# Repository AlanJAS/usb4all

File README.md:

# USB4all

USB4all es una placa para conectar sensores, actuadores y otros dispositivos electrónicos a una computadora mediante USB. Utiliza un **PIC18F4550** y organiza sus funcionalidades en módulos de firmware, con aplicaciones en el **Proyecto Butiá**.

El proyecto Butiá usa la placa USB4all (llamada USB4butia) con motores para crear una plataforma robótica educativa de bajo costo.

[Wiki Proyecto Butiá](https://www.fing.edu.uy/inco/proyectos/butia/mediawiki/index.php?title=Wiki_Buti%C3%A1)

Este repositorio reúne el firmware, el bootloader, diseños de placas, documentación técnica y una herramienta para grabar la aplicación por USB.

## Contenido

| Directorio | Contenido |
| --- | --- |
| [firmware/u4a2](firmware/u4a2/) | Firmware principal y módulos de usuario. |
| [firmware/bootloader](firmware/bootloader/) | Bootloader para instalar y actualizar la aplicación. |
| [fsusb-0.1.11-2](fsusb-0.1.11-2/) | Utilidad de programación USB incluida en el repositorio. |
| [pcb](pcb/) | Diseños de placas, sensores, actuadores y accesorios. |
| [doc](doc/) | Manuales, documentación del proyecto y del microcontrolador. |
| [usb4all_kernel_module](usb4all_kernel_module/) | Código histórico de un módulo para el kernel de Linux. |

## Ramas y herramientas

- **`master`**: desarrollo original, con proyectos para MPLAB C18.
- **[`xc8`](https://github.com/AlanJAS/usb4all/tree/xc8)**: migración a MPLAB XC8, con Makefiles independientes para la aplicación y el bootloader.

**Los comandos de compilación de este README corresponden a la rama `xc8`.** Los módulos opcionales y ejemplos históricos no están necesariamente migrados.

```sh
git clone --branch xc8 https://github.com/AlanJAS/usb4all.git
cd usb4all
```

Si ya tenés el repositorio:

```sh
git fetch origin
git switch xc8
```

## Compilar con XC8

### Requisitos

- GNU Make.
- MPLAB XC8 para PIC; los Makefiles están configurados para **XC8 4.00**.
- Pack **Microchip PIC18Fxxxx_DFP 1.7.171**.
- Python 3.9 o posterior para las comprobaciones de la aplicación.

El compilador y el pack de dispositivos se obtienen por separado:

- [MPLAB XC8](https://www.microchip.com/en-us/tools-resources/develop/mplab-xc-compilers/xc8)
- [Microchip Device Packs](https://packs.download.microchip.com/)

Los Makefiles utilizan estas rutas predeterminadas en Linux:

```text
XC8=/opt/microchip/xc8/v4.00/bin/xc8-cc
DFP=/opt/microchip/mplabx/v6.35/packs/Microchip/PIC18Fxxxx_DFP/1.7.171/xc8
```

`DFP` debe apuntar al subdirectorio `xc8` del pack.

### Aplicación

Desde la raíz del repositorio:

```sh
make -C firmware/u4a2
```

También podés ejecutar `make` directamente dentro de `firmware/u4a2`. El objetivo predeterminado compila y ejecuta las comprobaciones de la imagen.

Archivo para grabar por USB:

```text
firmware/u4a2/build/xc8/usb4all2.hex
```

Para repetir las comprobaciones o limpiar los resultados:

```sh
make -C firmware/u4a2 check
make -C firmware/u4a2 clean
```

### Bootloader

```sh
make -C firmware/bootloader
```

Archivo para grabar con un programador de hardware:

```text
firmware/bootloader/build/xc8/bootloader.hex
```

Para limpiar:

```sh
make -C firmware/bootloader clean
```

### Usar otras rutas

Las variables se pueden sobrescribir en la línea de comandos de cualquiera de los dos Makefiles:

```sh
make -C firmware/u4a2 \
  XC8=/otra/ruta/bin/xc8-cc \
  DFP=/otra/ruta/PIC18Fxxxx_DFP/1.7.171/xc8
```

Si el compilador está en el `PATH`, usá `XC8=xc8-cc`.

### Proyectos MPLAB

Se conservan proyectos de distintas etapas del desarrollo. Para reproducir la compilación descrita aquí, usá los Makefiles de `firmware/u4a2` y `firmware/bootloader`. Los proyectos y scripts de enlace de C18 no deben reutilizarse directamente para enlazar con XC8.

## Grabar la placa

### 1. Instalar el bootloader

Si el PIC no tiene el bootloader, necesitás un programador de hardware compatible, como PICkit.

1. Compilá el bootloader.
2. Conectá el programador según el pinout de tu placa.
3. Seleccioná el PIC18F4550 en el software del programador.
4. Grabá y verificá `firmware/bootloader/build/xc8/bootloader.hex`.

Luego podés cargar la aplicación por USB. **El HEX de la aplicación no incluye el bootloader**: en XC8 comienza en `0x08C0` y se genera sin bits de configuración.

### 2. Compilar fsusb

La utilidad incluida utiliza la API de **libusb 0.1** (`usb.h`, enlace con `-lusb`). Necesitás un compilador C, Make y las cabeceras y biblioteca compatibles con esa API; libusb 1.0 por sí sola no sustituye esta dependencia.

```sh
make -C fsusb-0.1.11-2
```

### 3. Entrar en modo bootloader

Con la placa conectada por USB:

1. Mantené presionado el botón de programación.
2. Pulsá y soltá el botón de reset.
3. Soltá el botón de programación.

Comprobá la identificación con:

```sh
lsusb
```

| Estado | VID:PID |
| --- | --- |
| Aplicación USB4all | `04d8:000c` |
| Bootloader | `04d8:000b` |

### 4. Grabar y ejecutar la aplicación

Desde la raíz del repositorio:

```sh
./fsusb-0.1.11-2/fsusb --program firmware/u4a2/build/xc8/usb4all2.hex
```

La opción `--program` graba y verifica. También podés verificar por separado:

```sh
./fsusb-0.1.11-2/fsusb --verify firmware/u4a2/build/xc8/usb4all2.hex
```

Para salir del bootloader y ejecutar la aplicación:

```sh
./fsusb-0.1.11-2/fsusb --reset
```

Comprobá que la placa vuelva a aparecer como `04d8:000c`.

Si el sistema deniega el acceso USB, revisá los permisos del dispositivo o las reglas udev de tu distribución. Para una operación puntual, podés ejecutar el comando de grabación con `sudo`.

## Arquitectura y módulos

El firmware base gestiona la comunicación USB, los módulos y los recursos compartidos. Cada módulo expone operaciones de inicialización, liberación y configuración, además de procesar sus comandos específicos.

En la rama `xc8`, los módulos activos se enumeran explícitamente en [module_registry.h](https://github.com/AlanJAS/usb4all/blob/xc8/firmware/u4a2/user/module_registry.h). Incluyen administración, detección de módulos, puertos, AX12, botones, motores y módulos de sensores y actuadores Butiá.

Para incorporar un módulo a esta compilación:

1. Implementá su descriptor y callbacks tomando como referencia un módulo activo de `firmware/u4a2/user/`.
2. Agregá sus fuentes y dependencias a `SOURCES` en el Makefile de la aplicación.
3. Declaralo y agregalo al final de `U4A_MODULES`, preservando el orden existente.
4. Compilá, ejecutá las comprobaciones y probá sus comandos en la placa.

Los índices dependen del orden del registro: el software de la computadora debe enumerar los módulos por nombre y no conservar índices de una imagen anterior. Los módulos compilados con C18 no son compatibles binariamente con XC8; hay que recompilar la aplicación.

## Comprobaciones y estado de la migración

La aplicación incluye comprobaciones de tamaños y disposición de estructuras, y un script que revisa el HEX y los símbolos generados: direcciones de la aplicación, vectores y ubicación de buffers USB, entre otros aspectos.

Estas comprobaciones no sustituyen las pruebas con la placa. La documentación de migración señala validaciones pendientes del intercambio USB, margen de pila y latencia bajo carga. Una compilación exitosa no demuestra por sí sola el funcionamiento completo en hardware.

El [documento de migración XC8](https://github.com/AlanJAS/usb4all/blob/xc8/firmware/u4a2/README-XC8.md) contiene detalles técnicos e historial de cambios. Algunas secciones conservan referencias a etapas anteriores, como `Makefile.xc8` o la ausencia de una migración del bootloader; para compilar, seguí los comandos anteriores y los Makefiles de la rama.

## Problemas frecuentes

| Problema | Qué revisar |
| --- | --- |
| No se encuentra `xc8-cc` | Sobrescribir `XC8` con la ruta de instalación. |
| Error al localizar el dispositivo o el pack | Revisar `DFP` y que termine en el subdirectorio `xc8`. |
| Falta `usb.h` o falla el enlace con `-lusb` | Instalar los archivos de desarrollo compatibles con libusb 0.1. |
| fsusb no detecta la placa para grabar | Comprobar el modo bootloader (`04d8:000b`), el cable y los permisos USB. |
| La placa no entra en modo bootloader | Comprobar que tenga instalado el bootloader y repetir la secuencia de botones. |
| La aplicación no arranca | Verificar la grabación, el bootloader, los bits de configuración y la compatibilidad del hardware. |

## Documentación y origen

- [USB4all: arquitectura y guía de uso](https://www.fing.edu.uy/inco/proyectos/butia/mediawiki/index.php?title=Usb4all)
- [Grabación del firmware](https://www.fing.edu.uy/inco/proyectos/butia/mediawiki/index.php?title=Usb4all#4._Grabando_el_Firmware)
- [Documentación incluida en el repositorio](doc/usb4all/)
- [Repositorio original en SourceForge](https://sourceforge.net/projects/usb4all/)

USB4all se originó como un trabajo de grado en Ingeniería en Computación de Aguirre, Fernández y Grossy. Su documentación y su integración con Butiá se publican en el sitio de la Facultad de Ingeniería de la Universidad de la República, Uruguay.

## Licencias

La documentación original presenta USB4all bajo **GNU GPL v2**. El repositorio también contiene componentes de terceros con avisos propios, incluidos fuentes de Microchip. Consultá las cabeceras y los archivos de licencia de cada componente antes de reutilizarlo o redistribuirlo.

La licencia de la utilidad fsusb está incluida en [fsusb-0.1.11-2/COPYING](fsusb-0.1.11-2/COPYING).

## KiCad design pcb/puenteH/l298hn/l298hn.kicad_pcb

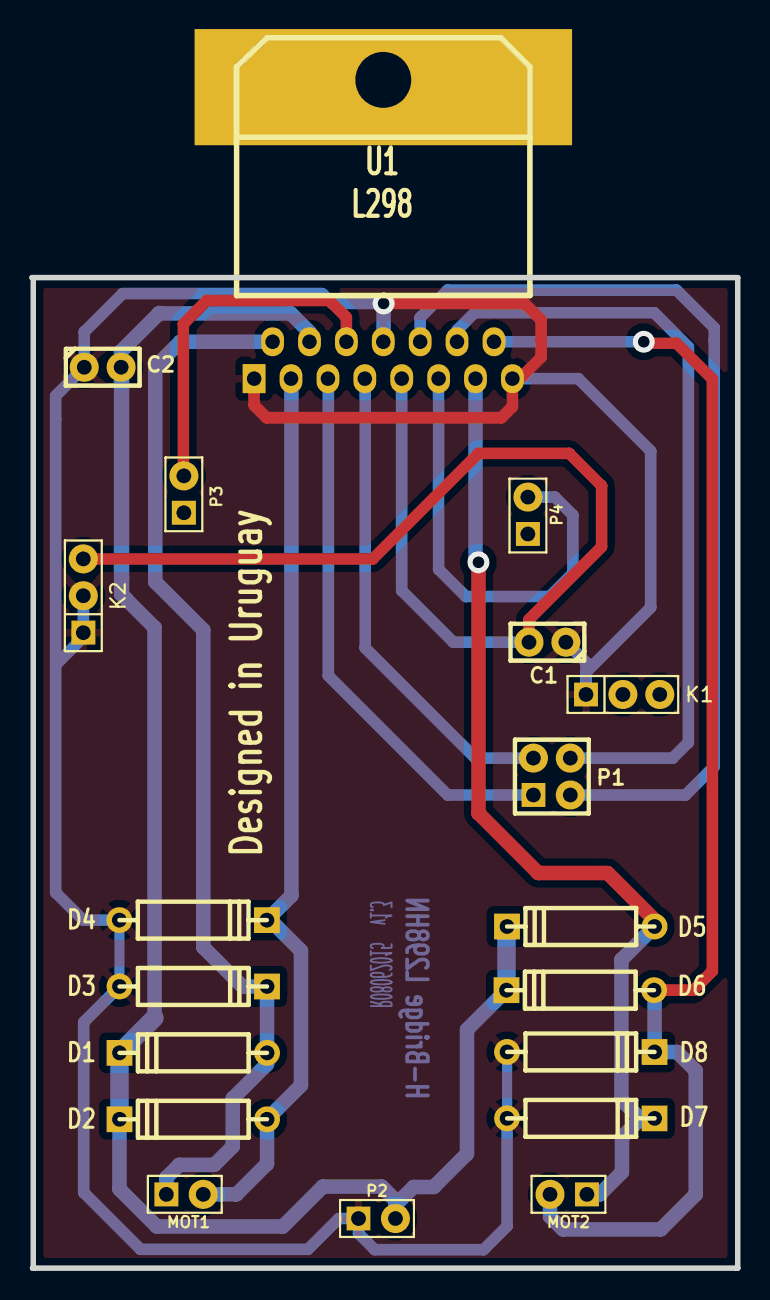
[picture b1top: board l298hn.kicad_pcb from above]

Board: 2 copper layers, 48.6 x 68.2 mm, 19 parts (0 on the bottom side), 13 nets.

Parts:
C1, C2: 100nF; C1
D1, D2, D3, D4, D5, D6, D7, D8: DIODE; D4
K1, K2: CONN_3; PIN_ARRAY_3X1
MOT1, MOT2: CONN_2; PIN_ARRAY_2X1
P1: CONN_2X2; PIN_ARRAY_2X2
P2: PWR; PIN_ARRAY_2X1
P3, P4: CONN_2; PIN_ARRAY_2X1
U1: L298; L298HN

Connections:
EnA: P3.2, U1.6
EnB: P4.2, U1.11
GND: C1.1, C2.1, D3.1, D4.1, D7.1, D8.1, K1.1, K2.1, K2.2, P2.1, U1.1, U1.8, U1.15
HK17: C1.2, K1.3, K2.3, U1.9
IN1: P1.1, U1.5
IN2: P1.2, U1.7
IN3: P1.3, U1.10
IN4: P1.4, U1.12
OUT1: D1.1, D3.2, MOT1.1, U1.2
OUT2: D2.1, D4.2, MOT1.2, U1.3
OUT3: D5.1, D7.2, MOT2.1, U1.13
OUT4: D6.1, D8.2, MOT2.2, U1.14
Vcc_12: C2.2, D1.2, D2.2, D5.2, D6.2, P2.2, U1.4

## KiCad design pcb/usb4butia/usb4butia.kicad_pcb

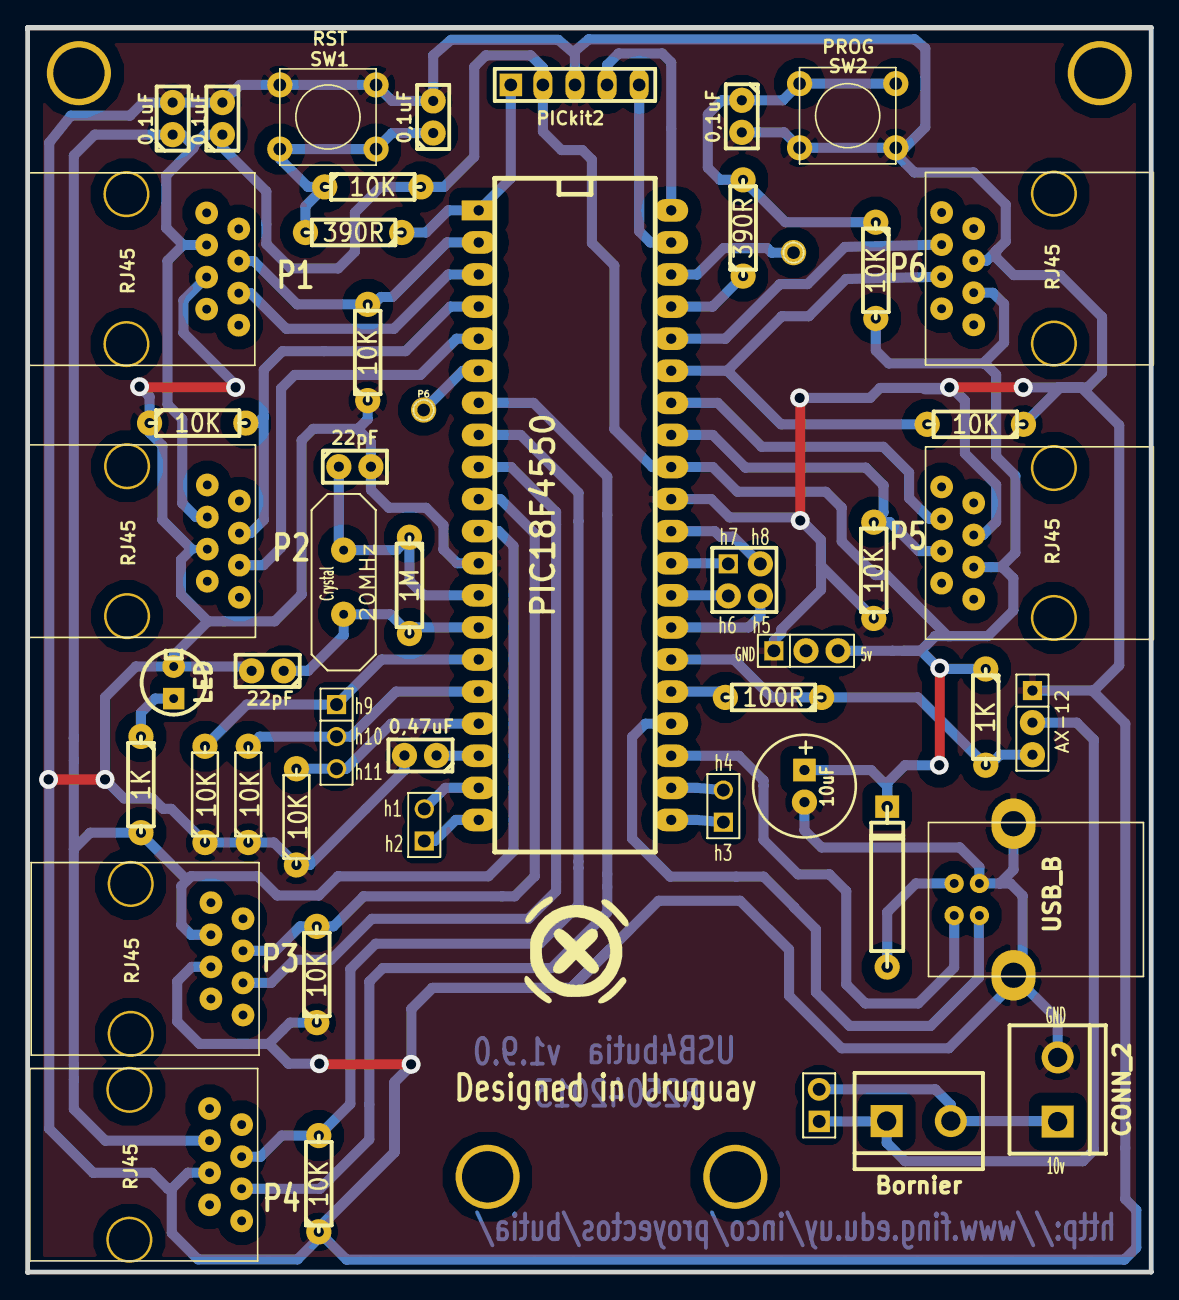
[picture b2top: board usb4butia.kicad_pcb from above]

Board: 2 copper layers, 88.9 x 98.5 mm, 50 parts (0 on the bottom side), 44 nets.

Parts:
C1, C2: 22pF; C1
C3, C7, C8, C9: 0,1uF; C1
C4: 0,47uF; C1
C10: 10uF; C1V8
D1: LED; LEDV
D2: 1N5819; D5
J1: USB_B
J2, J3, J4, J5, J6, J7: RJ45; RJ45_8
K1: AX-12; PIN_ARRAY_3X1
K2, K3: CONN_3; PIN_ARRAY_3X1
P1: PICkit2; PIN_ARRAY_5x1
P3, P4, P9: CONN_2; PIN_ARRAY_2X1
P5: CONN_4; PIN_ARRAY_2X2
P6, P7: CONN_1; PINTST
P13: Bornier; bornier2
P14: CONN_2; bornier2
R1, R14: 1K; R3
R2: 1M; R3
R3, R6, R7, R8, R9, R10, R12, R13, R15, R16, R17: 10K; R3
R4, R5: 390R; R3
R11: 100R; R3
SW1: RST; SW_PUSH_SMALL
SW2: PROG; SW_PUSH_SMALL
U1: PIC18F4550; 40DIP-ELL600
X1: 20MHz; HC-18UV

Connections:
AN1: J2.6, U1.3
AN3: J3.6, U1.5
AN4: J7.6, U1.7
AN6: J6.6, U1.9
AN9: J4.6, U1.36
AN10: J5.6, U1.34
D+: J1.3, U1.24
D-: J1.2, U1.23
GND: C1.2, C2.2, C3.2, C4.2, C7.2, C8.2, C9.2, C10.2, D1.2, J1.4, J1.5, J1.6, J2.5, J3.5, J4.5, J5.5, J6.5, J7.5, K1.1, K3.1, P1.3, P14.2, R7.1, R8.1, R9.1, R10.1, R12.1, R13.1, R15.1, R16.1, R17.1, SW1.1, SW2.2, U1.12, U1.31
HK6: P6.1, U1.6
HK15: K2.1, R15.2, U1.15
HK16: K2.2, R16.2, U1.16
HK17: K2.3, R17.2, U1.17
HK19: P4.2, U1.19
HK20: P4.1, U1.20
HK21: P3.1, U1.21
HK22: P3.2, U1.22
HK27: P5.4, U1.27
HK28: P5.3, U1.28
HK29: P5.1, U1.29
HK30: P5.2, U1.30
HK38: P7.1, U1.38
unnamed: C7.1, R5.2, R6.1, SW2.1
unnamed: C3.1, R3.1, R4.2, SW1.2
unnamed: D1.1, R1.1
unnamed: D2.1, J1.1
unnamed: R11.2, U1.25
OSC1: C1.1, R2.1, U1.13, X1.2
OSC2: C2.1, R2.2, U1.14, X1.1
RB4: R5.1, U1.37
RB6: P1.5, U1.39
RB7: P1.4, U1.40
VDC10: K1.2, P9.1, P13.1
VDC10_i: P9.2, P13.2, P14.1
VDD: C8.1, C9.1, C10.1, D2.2, J2.3, J3.3, J4.3, J5.3, J6.3, J7.3, K3.3, P1.2, R1.2, R3.2, R6.2, R14.1, U1.11, U1.32
Vpp: P1.1, R4.1, U1.1
Vusb: C4.1, U1.18
data: K1.3, R11.1, R14.2, U1.26
idAN0: J2.4, R7.2, U1.2
idAN2: J3.4, R8.2, U1.4
idAN5: J7.4, R13.2, U1.8
idAN7: J6.4, R12.2, U1.10
idAN8: J4.4, R9.2, U1.35
idAN12: J5.4, R10.2, U1.33

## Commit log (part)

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2012-07-24 move a 4 wheels butiá
2012-07-24 fixed copy-paste error
2012-08-06 Tests for serial emulation with USB CDC (communication device class) for pic 18F4550
2012-08-10 fixed problem with compiler and shifing bits, more info see http://www.microchip.com/forums/m135395.aspx
2012-08-10 fixed turning led on @ init, sorry aylen for the bug injection :P and added a temp function for getPosition
2012-09-15 bus_ax12 module
2012-09-15 resolving copy paste errors
2012-09-17 cleanup and some redundant serial initialization remove
2012-11-24 added a coper try... logo butia
2012-11-24 logobutia, some progrees
2012-11-27 ok, NO WAY OUT\!\!\!
2012-12-04 trying component instad of coper layer..., seens TO WORKS
2012-12-04 LOGO WORKS, now only need to relocate and scale
2012-12-05 modif to module
2012-12-05 copper logo seens to work
2012-12-05 working copper logo
2012-12-05 added copper logo
2012-12-14 Add AllSensors for order + key chain
2013-11-03 trying to make work infrared sensor for measuring time with high resolution. this is part of the work together with guzman trinidad form física con xo proyect I have some problems with pnp compilatio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
2013-11-03 for backup ...
2013-11-08 adding more time for timer interrupt for testing register timmer event only in counter state stay in polling to detect more fast the edges in the finite state machine
2013-11-08 seems to work...
2013-11-08 another aproach using timers instead of polling in the module. I don't think this is a good solution
2013-12-12 add led, not finish yet
2013-12-12 distance module sensor v1.9.1
2013-12-12 distance module sensor v2.0
2013-12-13 update plantilla_allsen with the new distance module
2014-01-31 module grey taked away from module ligth
2014-04-21 fix problems
2014-08-07 Fix capacitor problem v1.2
2015-01-23 Generic sensor working
2015-01-24 Usb4butia 1.9 with logo
2015-06-08 shield v1.3
2015-06-11 fix hk17 link
